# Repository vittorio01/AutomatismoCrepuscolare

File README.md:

# AutomatismoCrepuscolare
Un automatismo crepuscolare programmabile e intelligente che può essere applicato in molti campi

La scheda funziona con un semplice arduino pro mini.

In questa pagina è presente, oltre a uno schema elettrico del circuito principale e il programma per l'atmega328, anche una guida per l'utilizzo e la costruzione.
Per chi volesse costruire la scheda elettronica, sul file bottom.pdf è predente la faccia inferiore (l'unica) gia pronta per essere utilizzata (da notare che vanno mssi anche due ponticelli.

Questo progetto è ancora in fase sperimentale, quindi c'è la possibilità che non funzioni correttamente.

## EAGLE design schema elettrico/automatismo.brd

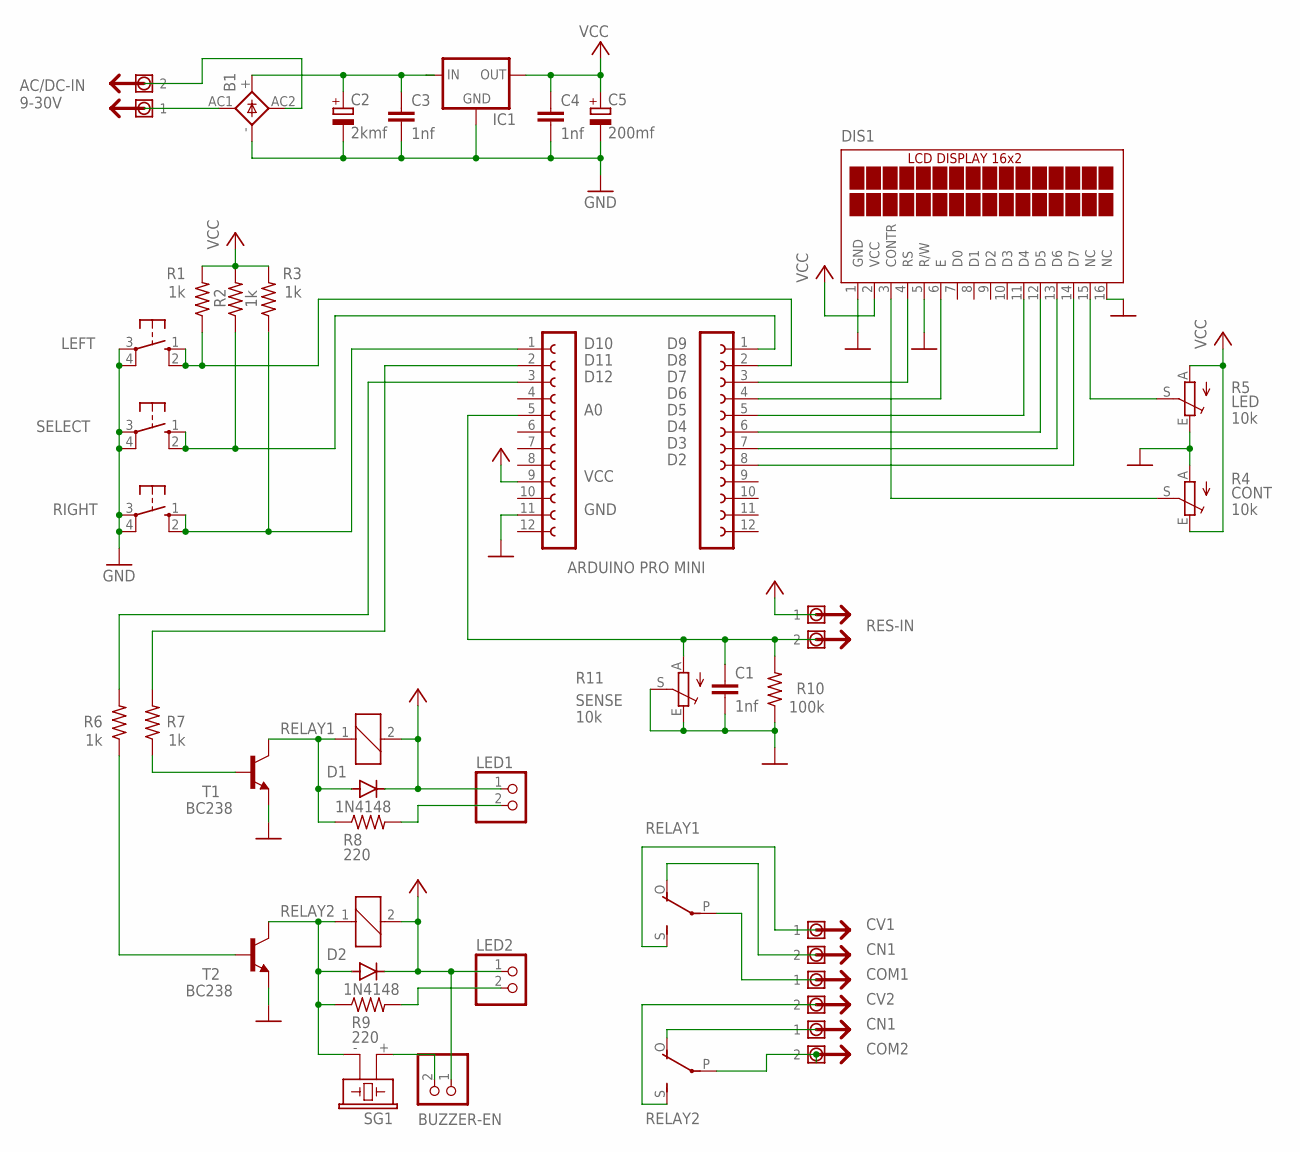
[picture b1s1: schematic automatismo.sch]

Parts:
B1: GBPC1
BUZZER-EN: PINHD-1X2; 1X02
C1, C3, C4: 1nf; C050-030X075
C2: 2kmf; E5-10,5
C5: 200mf; E2,5-7
D1, D2: 1N4148; DO35-7
DIS1: TUXGR_16X2_R2
IC1: 78XXL
L1, L2: FE12-1; FE12
LED1, LED2: PINHD-1X2; 1X02
LEFT: 10-XX; B3F-10XX
R1, R2, R3, R6, R7: 1k; 0207/10
R4, R5, R11: 10k; CA9V
R8, R9: 220; 0207/10
R10: 100k; 0207/10
RELAY1, RELAY2: E3206S
RIGHT: 10-XX; B3F-10XX
SELECT: 10-XX; B3F-10XX
SG1: F/CM12P
T1, T2: BC238; TO92
U$1, U$2, U$3, U$4, U$5: WIRE-OUT

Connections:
A0: C1.1, L2.5, R10.2, R11.A, U$4.P$2 (2)
CONTR: DIS1.3 (CONTR), R4.S
D2: DIS1.14 (D7), L1.8
D3: DIS1.13 (D6), L1.7
D4: DIS1.12 (D5), L1.6
D5: DIS1.11 (D4), L1.5
D6: DIS1.6 (E), L1.4
D7: DIS1.4 (RS), L1.3
D8: L1.2, LEFT.1 (S), LEFT.2 (S1), R1.1
D9: L1.1, R2.1, SELECT.1 (S), SELECT.2 (S1)
D10: L2.1, R3.1, RIGHT.1 (S), RIGHT.2 (S1)
D11: L2.2, R7.2
D12: L2.3, R6.2
GND: B1.-, C1.2, C2.-, C3.2, C4.2, C5.-, DIS1.1 (GND), DIS1.5 (R/W), DIS1.16 (NC), IC1.GND, L2.11, LEFT.3, LEFT.4 (P1), R4.A, R5.E, R10.1, R11.E, R11.S, RIGHT.3, RIGHT.4 (P1), SELECT.3, SELECT.4 (P1), T1.1 (E), T2.1 (E)
LED+: DIS1.15 (NC), R5.S
unnamed: R7.1, T1.2 (B)
unnamed: R6.1, T2.2 (B)
unnamed: D1.A, R8.1, RELAY1.1, T1.3 (C)
unnamed: D2.A, R9.1, RELAY2.1, SG1.- (2), T2.3 (C)
unnamed: LED1.2, R8.2
unnamed: LED2.2, R9.2
unnamed: RELAY1.P, U$2.P$1 (1)
unnamed: RELAY1.O, U$1.P$2 (2)
unnamed: RELAY1.S, U$1.P$1 (1)
unnamed: RELAY2.P, U$3.P$2 (2)
unnamed: RELAY2.O, U$3.P$1 (1)
unnamed: RELAY2.S, U$2.P$2 (2)
unnamed: BUZZER-EN.2, SG1.+ (1)
unnamed: B1.AC1, U$5.P$1 (1)
unnamed: B1.AC2, U$5.P$2 (2)
unnamed: B1.+, C2.+, C3.1, IC1.IN
VCC: BUZZER-EN.1, C4.1, C5.+, D1.C, D2.C, DIS1.2 (VCC), IC1.OUT, L2.9, LED1.1, LED2.1, R1.2, R2.2, R3.2, R4.E, R5.A, RELAY1.2, RELAY2.2, U$4.P$1 (1)

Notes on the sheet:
COM1
CN1
CV1
COM2
CV2
CONT
LED
RES-IN
SENSE
AC/DC-IN 9-30V
ARDUINO PRO MINI

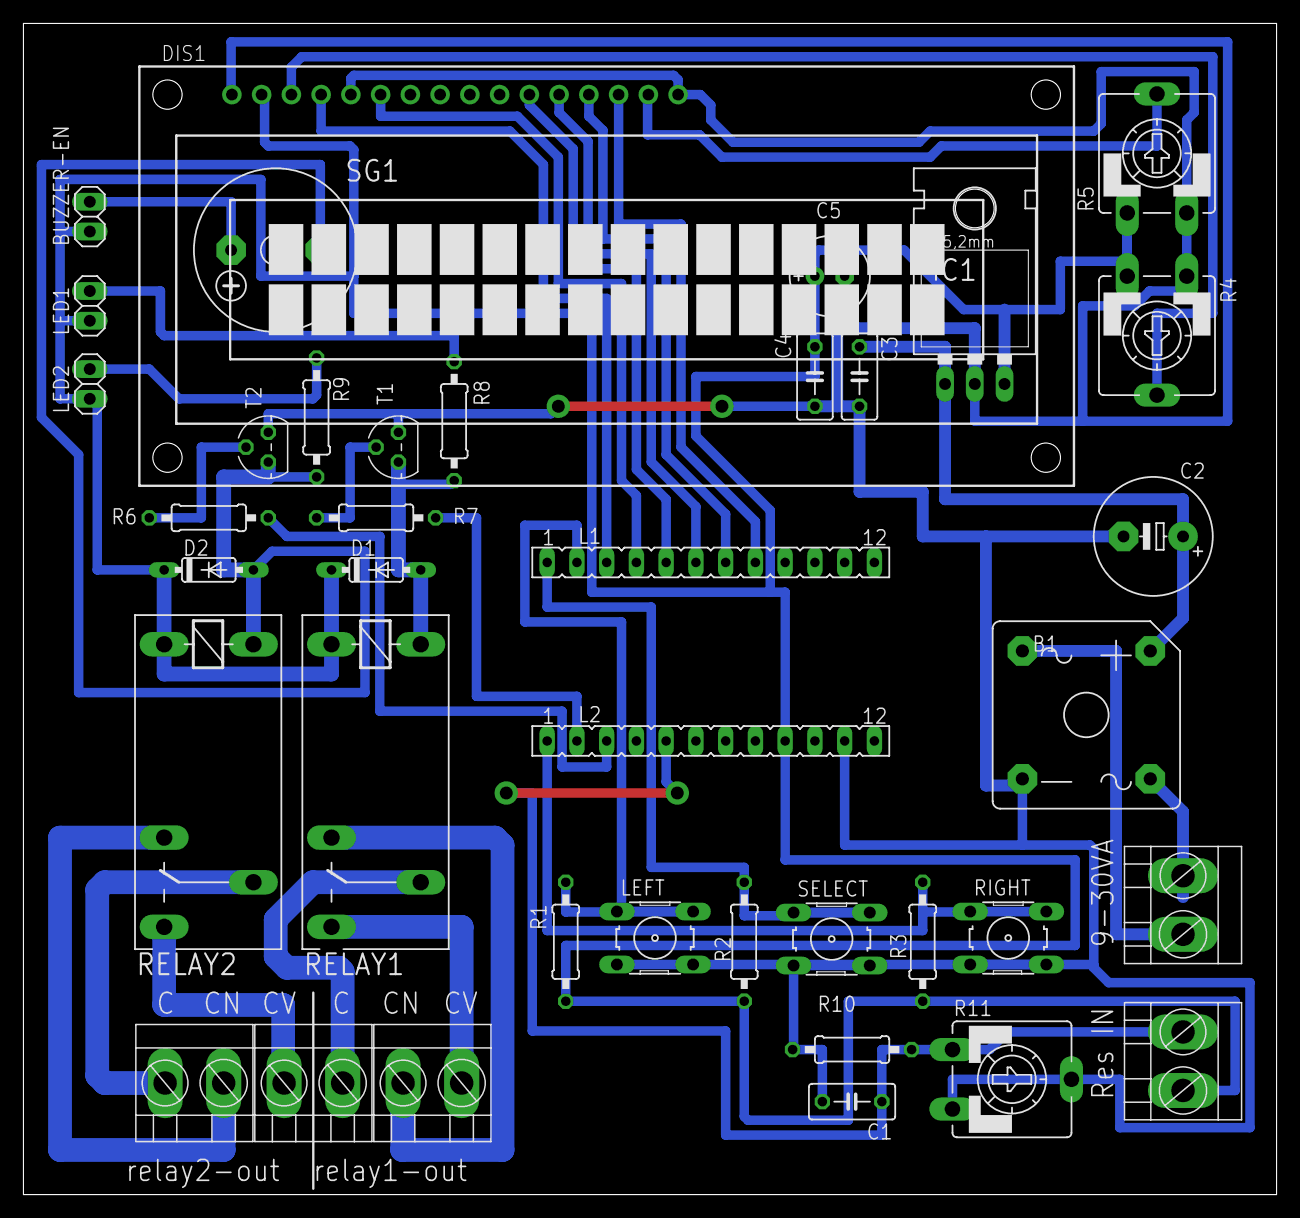
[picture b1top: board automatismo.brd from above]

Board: 2 copper layers, 107.0 x 100.0 mm, 39 parts (0 on the bottom side), 32 nets.

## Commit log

2025-01-14 aggiornato lo schema elettrico
2025-08-24 added base structure
2025-08-24 added lcd library
2025-08-25 added display class
2025-08-27 added display functions
2025-08-27 added functionalities
2025-08-29 addons
2025-09-05 added all functionalities
2025-09-05 bugfix
2025-09-05 optimizations
2025-09-05 refactoring progetto
